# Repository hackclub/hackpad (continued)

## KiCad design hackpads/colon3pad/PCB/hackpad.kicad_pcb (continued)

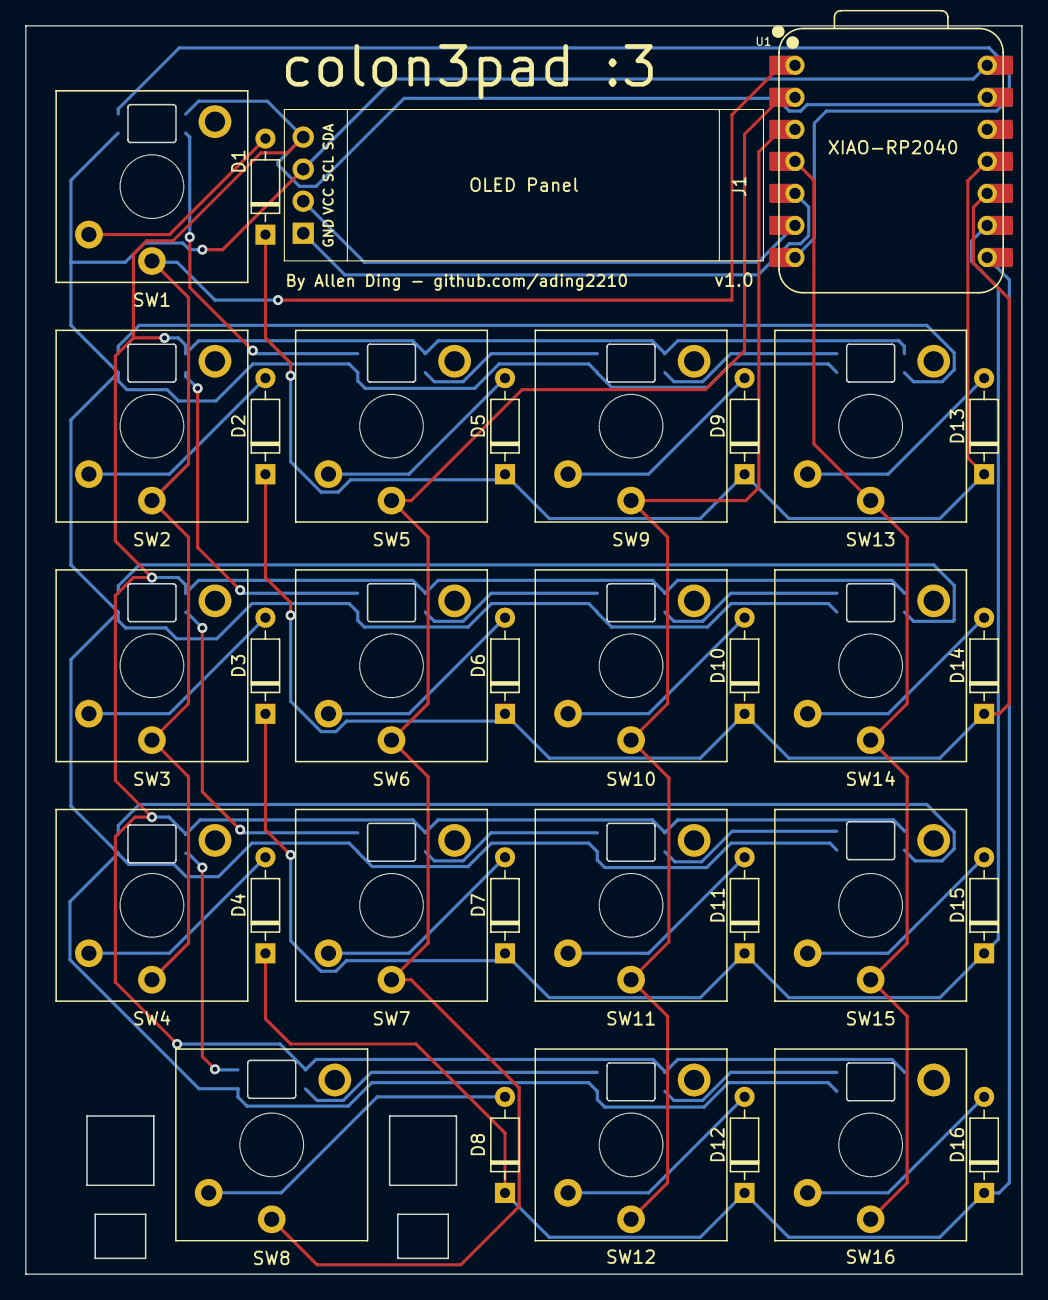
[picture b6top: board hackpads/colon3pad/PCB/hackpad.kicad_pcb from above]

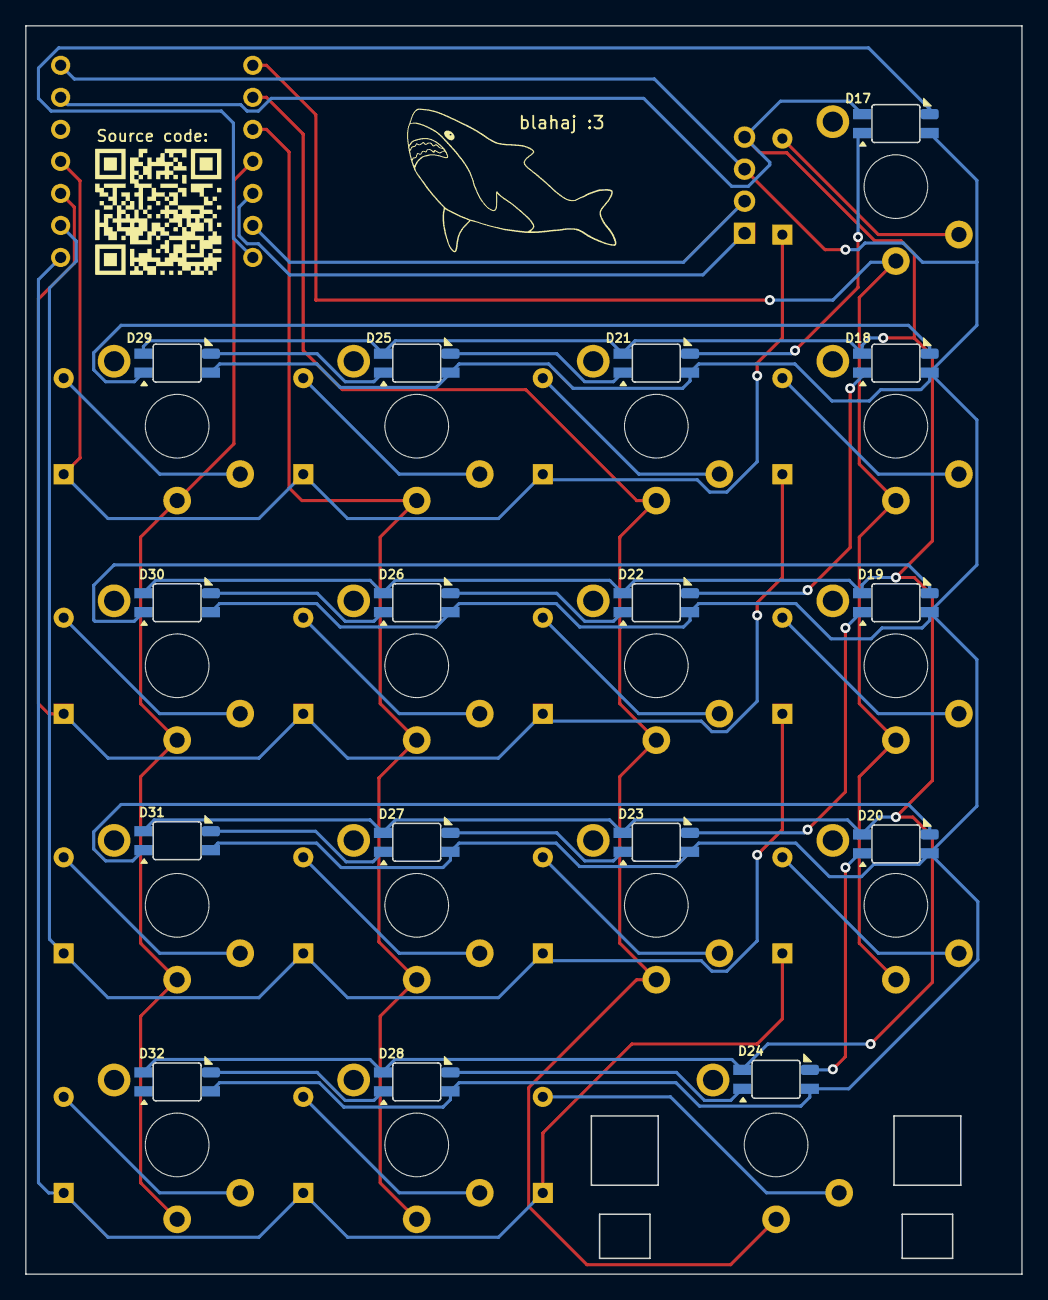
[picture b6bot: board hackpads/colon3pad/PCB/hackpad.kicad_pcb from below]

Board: 2 copper layers, 79.0 x 99.0 mm, 51 parts (16 on the bottom side), 44 nets.

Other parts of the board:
2u: Choc-2u-solder

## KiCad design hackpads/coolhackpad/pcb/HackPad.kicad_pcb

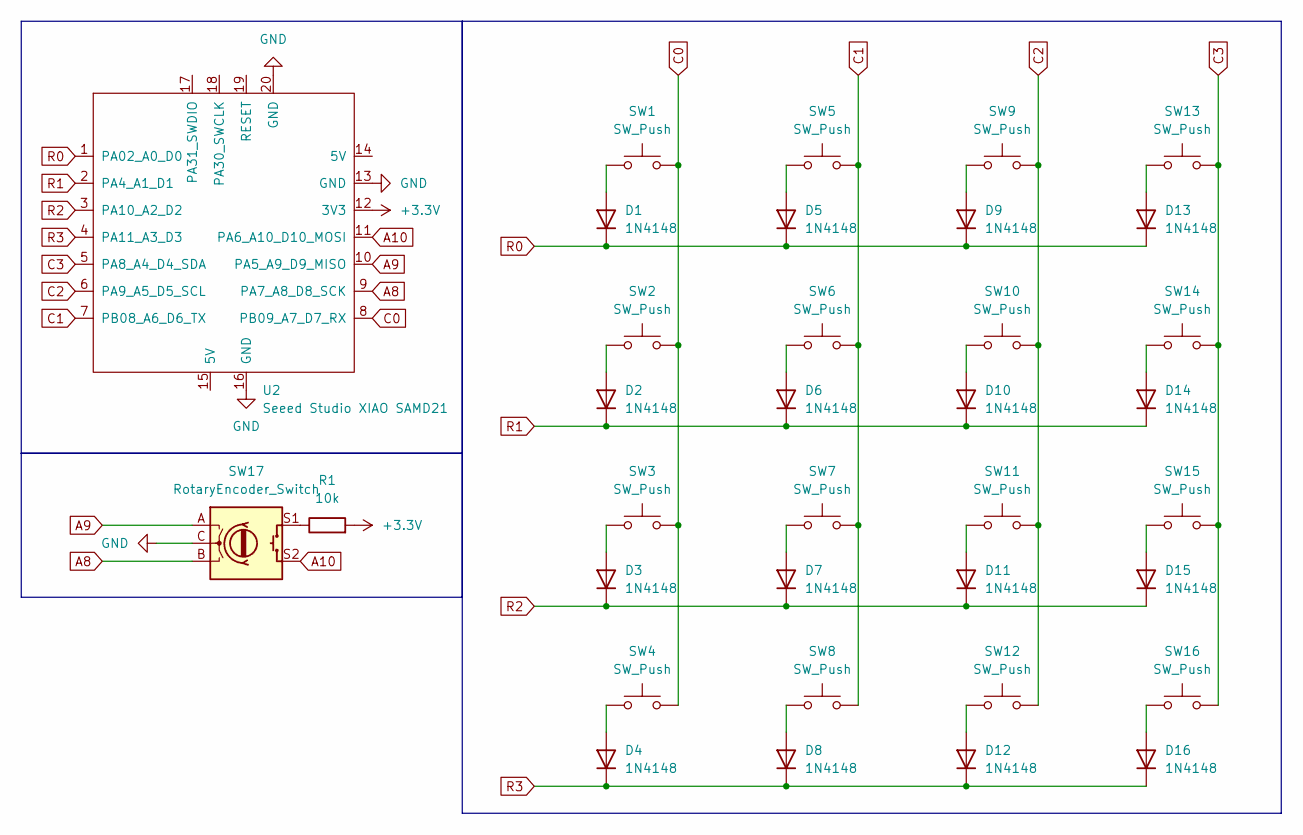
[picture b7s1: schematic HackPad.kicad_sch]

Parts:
D1, D2, D3, D4, D5, D6, D7, D8, D9, D10, D11, D12, D13, D14, D15, D16: 1N4148; D_DO-35_SOD27_P7.62mm_Horizontal
R1: 10k; R_Axial_DIN0207_L6.3mm_D2.5mm_P7.62mm_Horizontal
SW1, SW2, SW3, SW4, SW5, SW6, SW7, SW8, SW9, SW10, SW11, SW12, SW13, SW14, SW15, SW16: SW_Push; SW_Cherry_MX_1.00u_PCB
SW17: RotaryEncoder_Switch; RotaryEncoder_Alps_EC11E-Switch_Vertical_H20mm
U2: Seeed Studio XIAO SAMD21; XIAO-Generic-Thruhole-14P-2.54-21X17.8MM

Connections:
+3.3V: R1.2, U2.12 (3V3)
A8: SW17.B, U2.9 (PA7_A8_D8_SCK)
A9: SW17.A, U2.10 (PA5_A9_D9_MISO)
A10: SW17.S2, U2.11 (PA6_A10_D10_MOSI)
C0: SW1.2, SW2.2, SW3.2, SW4.2, U2.8 (PB09_A7_D7_RX)
C1: SW5.2, SW6.2, SW7.2, SW8.2, U2.7 (PB08_A6_D6_TX)
C2: SW9.2, SW10.2, SW11.2, SW12.2, U2.6 (PA9_A5_D5_SCL)
C3: SW13.2, SW14.2, SW15.2, SW16.2, U2.5 (PA8_A4_D4_SDA)
GND: SW17.C, U2.13 (GND), U2.16 (GND), U2.20 (GND)
unnamed: D1.2 (A), SW1.1
unnamed: D2.2 (A), SW2.1
unnamed: D3.2 (A), SW3.1
unnamed: D4.2 (A), SW4.1
unnamed: D5.2 (A), SW5.1
unnamed: D6.2 (A), SW6.1
unnamed: D7.2 (A), SW7.1
unnamed: D8.2 (A), SW8.1
unnamed: D9.2 (A), SW9.1
unnamed: D10.2 (A), SW10.1
unnamed: D11.2 (A), SW11.1
unnamed: D12.2 (A), SW12.1
unnamed: D13.2 (A), SW13.1
unnamed: D14.2 (A), SW14.1
unnamed: D15.2 (A), SW15.1
unnamed: D16.2 (A), SW16.1
unnamed: R1.1, SW17.S1
R0: D1.1 (K), D5.1 (K), D9.1 (K), D13.1 (K), U2.1 (PA02_A0_D0)
R1: D2.1 (K), D6.1 (K), D10.1 (K), D14.1 (K), U2.2 (PA4_A1_D1)
R2: D3.1 (K), D7.1 (K), D11.1 (K), D15.1 (K), U2.3 (PA10_A2_D2)
R3: D4.1 (K), D8.1 (K), D12.1 (K), D16.1 (K), U2.4 (PA11_A3_D3)

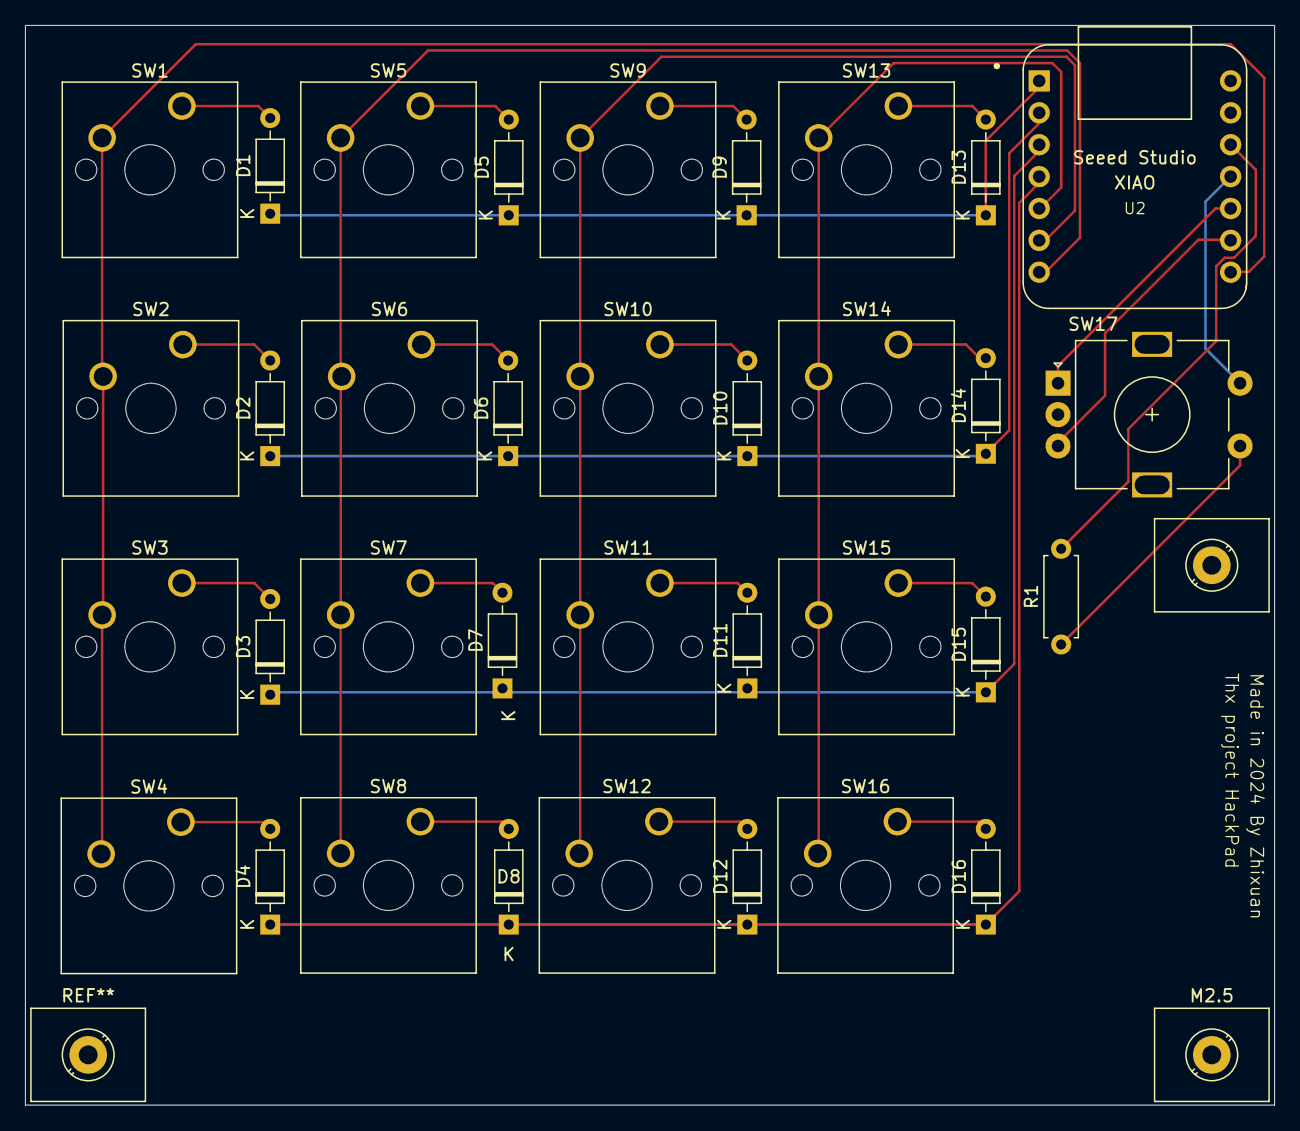
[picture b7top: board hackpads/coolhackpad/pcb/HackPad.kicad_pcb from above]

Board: 2 copper layers, 99.5 x 86.0 mm, 36 parts (0 on the bottom side), 30 nets.

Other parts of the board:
M2.5: TerminalBlock_MetzConnect_360271_1x01_Horizontal_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; TerminalBlock_MetzConnect_360271_1x01_Horizontal_ScrewM3.0_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
